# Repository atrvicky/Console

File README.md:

# Console
PCB design of the Hyp Console - an esp8266 powered board, powered by microPython and a ton of embedded functionalities out of the box.

The console has the following features:

* I2C Expander.
* Native LCD support.
* Native support for upto 3 external LEDs (PWM enabled).
* One default LED (PWM enabled).
* Native support for upto 4 DC motors, 2 Steppers, one ultrasound sensor and two infrared sensors.
* Integrated accelerometer with freefall detection, tap detection, doub click detection.
* Dedicated PWM controller and I2C port expander.
* MOSFET controllers for motors for enhanced current delivery to the motors.
* 9 GPIO pins.
* Stabilised 3V3 and 5V outputs.

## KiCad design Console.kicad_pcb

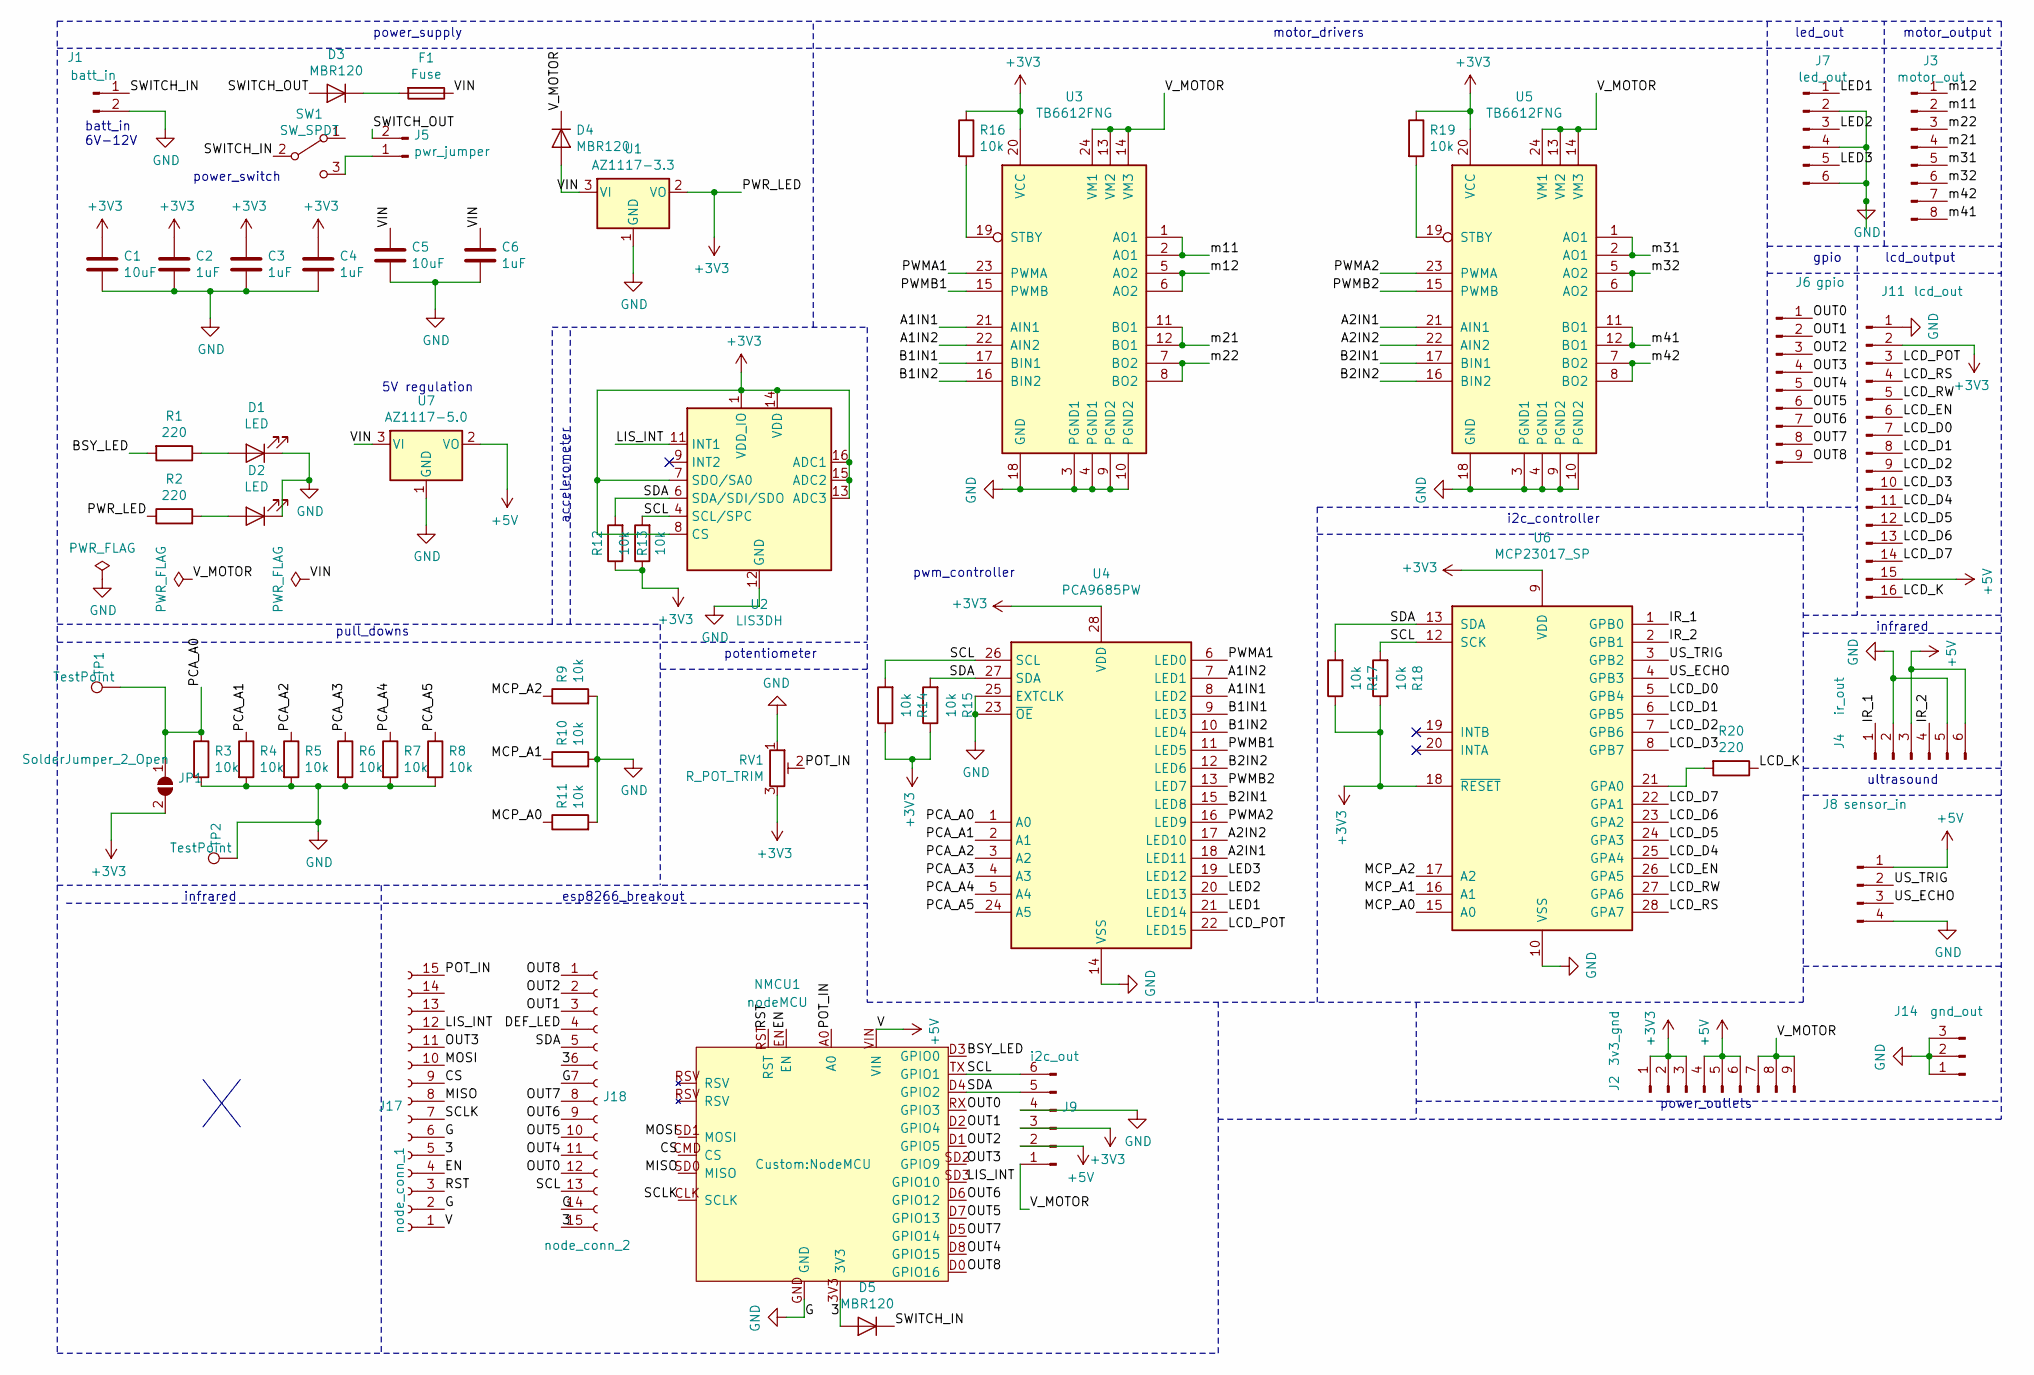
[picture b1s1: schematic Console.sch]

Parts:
C1, C5: 10uF; C_0805_2012Metric
C2, C3, C4, C6: 1uF; C_0805_2012Metric
D1, D2: LED; LED_0805_2012Metric
D3, D4, D5: MBR120; D_0805_2012Metric
F1: Fuse; Fuse_1206_3216Metric
J1: batt_in; PinHeader_1x02_P2.54mm_Vertical
J2: 3v3_gnd; PinHeader_1x09_P2.54mm_Vertical
J3: motor_out; PinHeader_1x08_P2.54mm_Vertical
J4: ir_out; PinHeader_1x06_P2.54mm_Vertical
J5: pwr_jumper; PinHeader_1x02_P2.54mm_Vertical
J6: gpio; PinHeader_1x09_P2.54mm_Vertical
J7: led_out; PinHeader_1x06_P2.54mm_Vertical
J8: sensor_in; PinHeader_1x04_P2.54mm_Vertical
J9: i2c_out; PinHeader_1x06_P2.54mm_Vertical
J11: lcd_out; PinHeader_1x16_P2.54mm_Vertical
J14: gnd_out; PinHeader_1x03_P2.54mm_Vertical
J17: node_conn_1; PinSocket_1x15_P2.54mm_Vertical
J18: node_conn_2; PinSocket_1x15_P2.54mm_Vertical
JP1: SolderJumper_2_Open; SolderJumper-2_P1.3mm_Open_RoundedPad1.0x1.5mm
NMCU1: nodeMCU; NodeMCU
R1, R2, R20: 220; R_0805_2012Metric
R3, R4, R5, R6, R7, R8, R9, R10, R11, R12, R13, R14, R15, R16, R17, R18, R19: 10k; R_0805_2012Metric
RV1: R_POT_TRIM; Potentiometer_Bourns_PTA2043_Single_Slide
SW1: SW_SPDT; SW_CuK_OS102011MA1QN1_SPDT_Angled
TP1, TP2: TestPoint; TestPoint_Pad_1.5x1.5mm
U1: AZ1117-3.3; TO-252-3_TabPin2
U2: LIS3DH; LGA-16_3x3mm_P0.5mm_LayoutBorder3x5y
U3, U5: TB6612FNG; SSOP-24_5.3x8.2mm_P0.65mm
U4: PCA9685PW; TSSOP-28_4.4x9.7mm_P0.65mm
U6: MCP23017_SP; SOIC-28W_7.5x17.9mm_P1.27mm
U7: AZ1117-5.0; TO-252-3_TabPin2

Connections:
+3V3: C1.1, C2.1, C3.1, C4.1, J2.1, J2.2, J2.3, J9.3, J11.2, JP1.2 (B), R2.1, R12.1, R13.1, R14.1, R15.1, R16.1, R17.1, R18.1, R19.1, RV1.3, U1.2 (VO), U2.1 (VDD_IO), U2.7 (SDO/SA0), U2.8 (CS), U2.13 (ADC3), U2.14 (VDD), U2.15 (ADC2), U2.16 (ADC1), U3.20 (VCC), U4.28 (VDD), U5.20 (VCC), U6.9 (VDD), U6.18 (~RESET~); also elsewhere on the board
+5V: J2.4, J2.5, J2.6, J4.3, J4.6, J8.1, J9.2, J11.15, J17.1, NMCU1.VIN, U7.2 (VO)
/3: D5.2 (A), J17.5, J18.6, J18.15, NMCU1.3V3
/A1IN1: U3.21 (AIN1), U4.8 (LED2)
/A1IN2: U3.22 (AIN2), U4.7 (LED1)
/A2IN1: U4.18 (LED11), U5.21 (AIN1)
/A2IN2: U4.17 (LED10), U5.22 (AIN2)
/B1IN1: U3.17 (BIN1), U4.9 (LED3)
/B1IN2: U3.16 (BIN2), U4.10 (LED4)
/B2IN1: U4.15 (LED8), U5.17 (BIN1)
/B2IN2: U4.12 (LED6), U5.16 (BIN2)
/BSY_LED: NMCU1.D3 (GPIO0), R1.2
/CS: J17.9, NMCU1.CMD (CS)
/DEF_LED: J18.4
/EN: J17.4, NMCU1.EN
/IR_1: J4.1, U6.1 (GPB0)
/IR_2: J4.4, U6.2 (GPB1)
/LCD_D0: J11.7, U6.5 (GPB4)
/LCD_D1: J11.8, U6.6 (GPB5)
/LCD_D2: J11.9, U6.7 (GPB6)
/LCD_D3: J11.10, U6.8 (GPB7)
/LCD_D4: J11.11, U6.25 (GPA4)
/LCD_D5: J11.12, U6.24 (GPA3)
/LCD_D6: J11.13, U6.23 (GPA2)
/LCD_D7: J11.14, U6.22 (GPA1)
/LCD_EN: J11.6, U6.26 (GPA5)
/LCD_K: J11.16, R20.1
/LCD_POT: J11.3, U4.22 (LED15)
/LCD_RS: J11.4, U6.28 (GPA7)
/LCD_RW: J11.5, U6.27 (GPA6)
/LED1: J7.1, U4.21 (LED14)
/LED2: J7.3, U4.20 (LED13)
/LED3: J7.5, U4.19 (LED12)
/LIS_INT: J17.12, NMCU1.SD3 (GPIO10), U2.11 (INT1)
/MCP_A0: R11.1, U6.15 (A0)
/MCP_A1: R10.1, U6.16 (A1)
/MCP_A2: R9.1, U6.17 (A2)
/MISO: J17.8, NMCU1.SD0 (MISO)
/MOSI: J17.10, NMCU1.SD1 (MOSI)
/OUT0: J6.1, J18.12, NMCU1.RX (GPIO3)
/OUT1: J6.2, J18.3, NMCU1.D2 (GPIO4)
/OUT2: J6.3, J18.2, NMCU1.D1 (GPIO5)
/OUT3: J6.4, J17.11, NMCU1.SD2 (GPIO9)
/OUT4: J6.5, J18.11, NMCU1.D8 (GPIO15)
/OUT5: J6.6, J18.10, NMCU1.D7 (GPIO13)
/OUT6: J6.7, J18.9, NMCU1.D6 (GPIO12)
/OUT7: J6.8, J18.8, NMCU1.D5 (GPIO14)
/OUT8: J6.9, J18.1, NMCU1.D0 (GPIO16)
/PCA_A0: JP1.1 (A), R3.1, TP1.1, U4.1 (A0)
/PCA_A1: R4.1, U4.2 (A1)
/PCA_A2: R5.1, U4.3 (A2)
/PCA_A3: R6.1, U4.4 (A3)
/PCA_A4: R7.1, U4.5 (A4)
/PCA_A5: R8.1, U4.24 (A5)
/POT_IN: J17.15, NMCU1.A0, RV1.2
/PWMA1: U3.23 (PWMA), U4.6 (LED0)
/PWMA2: U4.16 (LED9), U5.23 (PWMA)
/PWMB1: U3.15 (PWMB), U4.11 (LED5)
/PWMB2: U4.13 (LED7), U5.15 (PWMB)
/RST: J17.3, NMCU1.RST
/SCLK: J17.7, NMCU1.CLK (SCLK)
/SDA: J9.5, J18.5, NMCU1.D4 (GPIO2), R12.2, R15.2, R17.2, U2.6 (SDA/SDI/SDO), U4.27 (SDA), U6.13 (SDA)
/SWITCH_IN: D5.1 (K), J1.1, SW1.2 (B)
/SWITCH_OUT: D3.2 (A), J5.2
/US_ECHO: J8.3, U6.4 (GPB3)
/US_TRIG: J8.2, U6.3 (GPB2)
/VIN: C5.1, C6.1, D4.2 (A), F1.1, U1.3 (VI), U7.3 (VI); also elsewhere on the board
/V_MOTOR: D4.1 (K), J2.7, J2.8, J2.9, J9.1, U3.13 (VM2), U3.14 (VM3), U3.24 (VM1), U5.13 (VM2), U5.14 (VM3), U5.24 (VM1)
/m11: J3.2, U3.1 (AO1), U3.2 (AO1)
/m12: J3.1, U3.5 (AO2), U3.6 (AO2)
/m21: J3.4, U3.11 (BO1), U3.12 (BO1)
/m22: J3.3, U3.7 (BO2), U3.8 (BO2)
/m31: J3.5, U5.1 (AO1), U5.2 (AO1)
/m32: J3.6, U5.5 (AO2), U5.6 (AO2)
/m41: J3.8, U5.11 (BO1), U5.12 (BO1)
/m42: J3.7, U5.7 (BO2), U5.8 (BO2)
GND: C1.2, C2.2, C3.2, C4.2, C5.2, C6.2, D1.1 (K), D2.1 (K), J1.2, J4.2, J4.5, J7.2, J7.4, J7.6, J8.4, J9.4, J11.1, J14.1, J14.2, J14.3, J17.2, J17.6, J18.7, J18.14, NMCU1.GND, R3.2, R4.2, R5.2, R6.2, R7.2, R8.2, R9.2, R10.2, R11.2, RV1.1, TP2.1, U1.1 (GND), U2.5 (GND), U2.10 (GND), U2.12 (GND), U3.3 (PGND1), U3.4 (PGND1), U3.9 (PGND2), U3.10 (PGND2), U3.18 (GND), U4.14 (VSS), U4.23 (~OE), U4.25 (EXTCLK), U5.3 (PGND1), U5.4 (PGND1), U5.9 (PGND2), U5.10 (PGND2), U5.18 (GND), U6.10 (VSS), U7.1 (GND)
unnamed: D1.2 (A), R1.1
unnamed: D2.2 (A), R2.2
unnamed 79: D3.1 (K), F1.2; also elsewhere on the board
unnamed: J5.1, SW1.3 (C)
unnamed: R19.2, U5.19 (STBY)
unnamed: R20.2, U6.21 (GPA0)

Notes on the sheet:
batt_in 6V-12V
power_switch
pull_downs
power_supply
accelerometer
motor_drivers
pwm_controller
potentiometer
i2c_controller
esp8266_breakout
led_out
gpio
ultrasound
lcd_output
infrared
5V regulation
infrared
power_outlets
motor_output

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
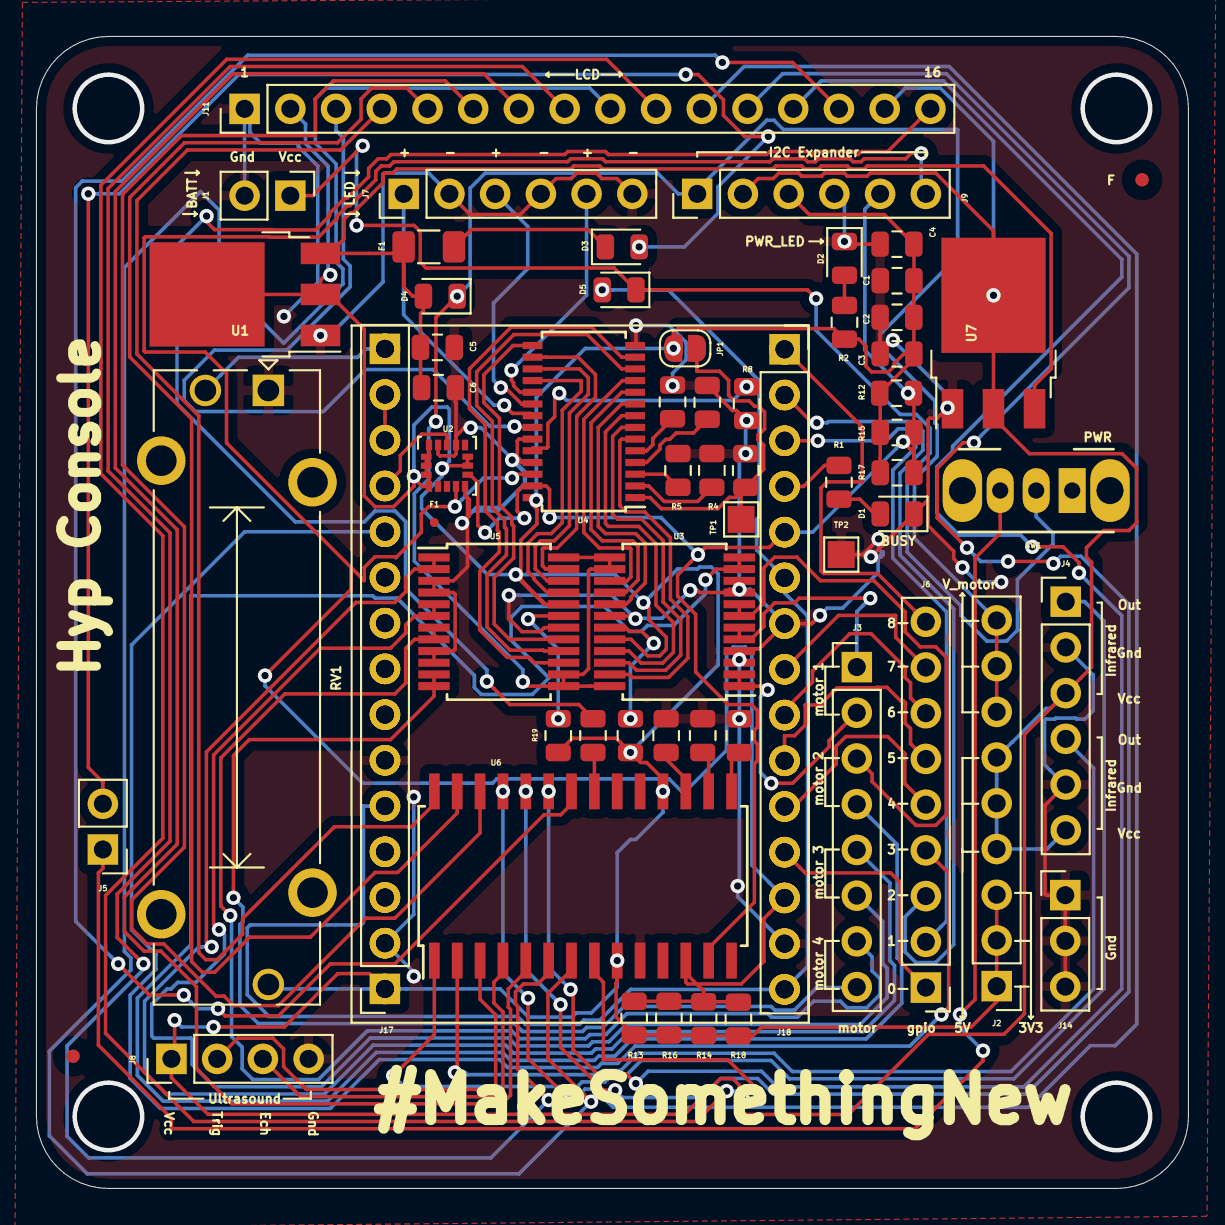
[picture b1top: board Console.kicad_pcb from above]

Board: 2 copper layers, 64.0 x 64.0 mm, 62 parts (0 on the bottom side), 84 nets.

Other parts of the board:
F: Fiducial_0.75mm_Mask2.25mm
F1#2: Fuse; Fuse_1206_3216Metric
F#2: Fiducial_0.75mm_Mask2.25mm
R16#2: 10k; R_0805_2012Metric

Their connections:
+3V3: R16#2.1; also elsewhere on the board
/VIN: F1#2.1; also elsewhere on the board
unnamed 79: F1#2.2; also elsewhere on the board

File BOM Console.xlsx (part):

Source: | G:\Studio\Hardware\kiCad\Console\Console.sch
Date: | 43774.806493055556
Tool: | Eeschema (5.1.0)-1
Generator: | G:\Program Files\KiCad\bin\scripting\plugins/bom_csv_grouped_by_value.py
Component Count: | 56
Individual Components:
Item | Qty | Reference(s) | Value | LibPart | Footprint | Datasheet
 |  | C1 | 10uF | Device:C | Capacitor_SMD:C_0805_2012Metric | ~
 |  | C2 | 1uF | Device:C | Capacitor_SMD:C_0805_2012Metric | ~
 |  | C3 | 1uF | Device:C | Capacitor_SMD:C_0805_2012Metric | ~
 |  | C4 | 1uF | Device:C | Capacitor_SMD:C_0805_2012Metric | ~
 |  | C5 | 10uF | Device:C | Capacitor_SMD:C_0805_2012Metric | ~
 |  | C6 | 1uF | Device:C | Capacitor_SMD:C_0805_2012Metric | ~
 |  | D1 | LED | Device:LED | LED_SMD:LED_0805_2012Metric | ~
 |  | D2 | LED | Device:LED | LED_SMD:LED_0805_2012Metric | ~
 |  | D3 | MBR120 | Device:D | Diode_SMD:D_0805_2012Metric | ~
 |  | D4 | MBR120 | Device:D | Diode_SMD:D_0805_2012Metric | ~
 |  | D5 | MBR120 | Device:D | Diode_SMD:D_0805_2012Metric | ~
 |  | F1 | Fuse | Device:Fuse | Fuse:Fuse_1206_3216Metric | ~
 |  | J1 | batt_in | Connector:Conn_01x02_Male | Connector_PinHeader_2.54mm:PinHeader_1x02_P2.54mm_Vertical | ~
 |  | J2 | 3v3_gnd | Connector:Conn_01x09_Male | Connector_PinHeader_2.54mm:PinHeader_1x09_P2.54mm_Vertical | ~
 |  | J3 | motor_out | Connector:Conn_01x08_Male | Connector_PinHeader_2.54mm:PinHeader_1x08_P2.54mm_Vertical | ~
 |  | J4 | ir_out | Connector:Conn_01x06_Male | Connector_PinHeader_2.54mm:PinHeader_1x06_P2.54mm_Vertical | ~
 |  | J5 | pwr_jumper | Connector:Conn_01x02_Male | Connector_PinHeader_2.54mm:PinHeader_1x02_P2.54mm_Vertical | ~
 |  | J6 | gpio | Connector:Conn_01x09_Male | Connector_PinHeader_2.54mm:PinHeader_1x09_P2.54mm_Vertical | ~
 |  | J7 | led_out | Connector:Conn_01x06_Male | Connector_PinHeader_2.54mm:PinHeader_1x06_P2.54mm_Vertical | ~
 |  | J8 | sensor_in | Connector:Conn_01x04_Male | Connector_PinHeader_2.54mm:PinHeader_1x04_P2.54mm_Vertical | ~
 |  | J9 | i2c_out | Connector:Conn_01x06_Male | Connector_PinHeader_2.54mm:PinHeader_1x06_P2.54mm_Vertical | ~
 |  | J11 | lcd_out | Connector:Conn_01x16_Male | Connector_PinHeader_2.54mm:PinHeader_1x16_P2.54mm_Vertical | ~
 |  | J14 | gnd_out | Connector:Conn_01x03_Male | Connector_PinHeader_2.54mm:PinHeader_1x03_P2.54mm_Vertical | ~
 |  | J17 | node_conn_1 | Connector:Conn_01x15_Female | Connector_PinSocket_2.54mm:PinSocket_1x15_P2.54mm_Vertical | ~
 |  | J18 | node_conn_2 | Connector:Conn_01x15_Female | Connector_PinSocket_2.54mm:PinSocket_1x15_P2.54mm_Vertical | ~
 |  | JP1 | SolderJumper_2_Open | Jumper:SolderJumper_2_Open | Jumper:SolderJumper-2_P1.3mm_Open_RoundedPad1.0x1.5mm | ~
 |  | NMCU1 | nodeMCU | MCU_Espressif:nodeMCU | Custom:NodeMCU
 |  | R1 | 220 | Device:R | Resistor_SMD:R_0805_2012Metric | ~
 |  | R2 | 220 | Device:R | Resistor_SMD:R_0805_2012Metric | ~
 |  | R3 | 10k | Device:R | Resistor_SMD:R_0805_2012Metric | ~
 |  | R4 | 10k | Device:R | Resistor_SMD:R_0805_2012Metric | ~
 |  | R5 | 10k | Device:R | Resistor_SMD:R_0805_2012Metric | ~
 |  | R6 | 10k | Device:R | Resistor_SMD:R_0805_2012Metric | ~
 |  | R7 | 10k | Device:R | Resistor_SMD:R_0805_2012Metric | ~
 |  | R8 | 10k | Device:R | Resistor_SMD:R_0805_2012Metric | ~
 |  | R9 | 10k | Device:R | Resistor_SMD:R_0805_2012Metric | ~
 |  | R10 | 10k | Device:R | Resistor_SMD:R_0805_2012Metric | ~
 |  | R11 | 10k | Device:R | Resistor_SMD:R_0805_2012Metric | ~
 |  | R12 | 10k | Device:R | Resistor_SMD:R_0805_2012Metric | ~
 |  | R13 | 10k | Device:R | Resistor_SMD:R_0805_2012Metric | ~
 |  | R14 | 10k | Device:R | Resistor_SMD:R_0805_2012Metric | ~
 |  | R15 | 10k | Device:R | Resistor_SMD:R_0805_2012Metric | ~
 |  | R16 | 10k | Device:R | Resistor_SMD:R_0805_2012Metric | ~
 |  | R17 | 10k | Device:R | Resistor_SMD:R_0805_2012Metric | ~
 |  | R18 | 10k | Device:R | Resistor_SMD:R_0805_2012Metric | ~
 |  | R19 | 10k | Device:R | Resistor_SMD:R_0805_2012Metric | ~
 |  | R20 | 220 | Device:R | Resistor_SMD:R_0805_2012Metric | ~
 |  | RV1 | R_POT_TRIM | Device:R_POT_TRIM | Potentiometer_THT:Potentiometer_Bourns_PTA2043_Single_Slide | ~
 |  | SW1 | SW_SPST | Switch:SW_SPST | Button_Switch_SMD:SW_DIP_SPSTx01_Slide_9.78x4.72mm_W8.61mm_P2.54mm | ~
 |  | U1 | AZ1117-3.3 | Regulator_Linear:AZ1117-3.3 | Package_TO_SOT_SMD:TO-252-3_TabPin2 | https://www.diodes.com/assets/Datasheets/AZ1117.pdf
 |  | U2 | LIS3DH | Sensor_Motion:LIS3DH | Package_LGA:LGA-16_3x3mm_P0.5mm_LayoutBorder3x5y | https://www.st.com/resource/en/datasheet/cd00274221.pdf
 |  | U3 | TB6612FNG | Driver_Motor:TB6612FNG | Package_SO:SSOP-24_5.3x8.2mm_P0.65mm | https://toshiba.semicon-storage.com/us/product/linear/motord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
 |  | U4 | PCA9685PW | Driver_LED:PCA9685PW | Package_SO:TSSOP-28_4.4x9.7mm_P0.65mm | http://www.nxp.com/documents/data_sheet/PCA9685.pdf
 |  | U5 | TB6612FNG | Driver_Motor:TB6612FNG | Package_SO:SSOP-24_5.3x8.2mm_P0.65mm | https://toshiba.semicon-storage.com/us/product/linear/motord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
 |  | U6 | MCP23017_SP | Interface_Expansion:MCP23017_SP | Package_SO:SOIC-28W_7.5x17.9mm_P1.27mm | http://ww1.microchip.com/downloads/en/DeviceDoc/20001952C.pdf
 |  | U7 | AZ1117-5.0 | Regulator_Linear:AZ1117-5.0 | Package_TO_SOT_SMD:TO-252-3_TabPin2 | https://www.diodes.com/assets/Datasheets/AZ1117.pdf
Collated Components:
Item | Qty | Reference(s) | Value | LibPart | Footprint | Datasheet
1 | 2 | C1, C5 | 10uF | Device:C | Capacitor_SMD:C_0805_2012Metric | ~
2 | 4 | C2, C3, C4, C6 | 1uF | Device:C | Capacitor_SMD:C_0805_2012Metric | ~
3 | 2 | D1, D2 | LED | Device:LED | LED_SMD:LED_0805_2012Metric | ~
4 | 3 | D3, D4, D5 | MBR120 | Device:D | Diode_SMD:D_0805_2012Metric | ~
5 | 1 | F1 | Fuse | Device:Fuse | Fuse:Fuse_1206_3216Metric | ~
6 | 1 | J1 | batt_in | Connector:Conn_01x02_Male | Connector_PinHeader_2.54mm:PinHeader_1x02_P2.54mm_Vertical | ~
7 | 1 | J2 | 3v3_gnd | Connector:Conn_01x09_Male | Connector_PinHeader_2.54mm:PinHeader_1x09_P2.54mm_Vertical | ~
8 | 1 | J3 | motor_out | Connector:Conn_01x08_Male | Connector_PinHeader_2.54mm:PinHeader_1x08_P2.54mm_Vertical | ~
9 | 1 | J4 | ir_out | Connector:Conn_01x06_Male | Connector_PinHeader_2.54mm:PinHeader_1x06_P2.54mm_Vertical | ~
10 | 1 | J5 | pwr_jumper | Connector:Conn_01x02_Male | Connector_PinHeader_2.54mm:PinHeader_1x02_P2.54mm_Vertical | ~
11 | 1 | J6 | gpio | Connector:Conn_01x09_Male | Connector_PinHeader_2.54mm:PinHeader_1x09_P2.54mm_Vertical | ~
12 | 1 | J7 | led_out | Connector:Conn_01x06_Male | Connector_PinHeader_2.54mm:PinHeader_1x06_P2.54mm_Vertical | ~
13 | 1 | J8 | sensor_in | Connector:Conn_01x04_Male | Connector_PinHeader_2.54mm:PinHeader_1x04_P2.54mm_Vertical | ~
14 | 1 | J9 | i2c_out | Connector:Conn_01x06_Male | Connector_PinHeader_2.54mm:PinHeader_1x06_P2.54mm_Vertical | ~
15 | 1 | J11 | lcd_out | Connector:Conn_01x16_Male | Connector_PinHeader_2.54mm:PinHeader_1x16_P2.54mm_Vertical | ~
16 | 1 | J14 | gnd_out | Connector:Conn_01x03_Male | Connector_PinHeader_2.54mm:PinHeader_1x03_P2.54mm_Vertical | ~
17 | 1 | J17 | node_conn_1 | Connector:Conn_01x15_Female | Connector_PinSocket_2.54mm:PinSocket_1x15_P2.54mm_Vertical | ~
18 | 1 | J18 | node_conn_2 | Connector:Conn_01x15_Female | Connector_PinSocket_2.54mm:PinSocket_1x15_P2.54mm_Vertical | ~
19 | 1 | JP1 | SolderJumper_2_Open | Jumper:SolderJumper_2_Open | Jumper:SolderJumper-2_P1.3mm_Open_RoundedPad1.0x1.5mm | ~
20 | 1 | NMCU1 | nodeMCU | MCU_Espressif:nodeMCU | Custom:NodeMCU
21 | 3 | R1, R2, R20 | 220 | Device:R | Resistor_SMD:R_0805_2012Metric | ~
22 | 17 | R3, R4, R5, R6, R7, R8, R9, R10, R11, R12, R13, R14, R15, R16, R17, R18, R19 | 10k | Device:R | Resistor_SMD:R_0805_2012Metric | ~
23 | 1 | RV1 | R_POT_TRIM | Device:R_POT_TRIM | Potentiometer_THT:Potentiometer_Bourns_PTA2043_Single_Slide | ~
24 | 1 | SW1 | SW_SPST | Switch:SW_SPST | Button_Switch_SMD:SW_DIP_SPSTx01_Slide_9.78x4.72mm_W8.61mm_P2.54mm | ~
25 | 1 | U1 | AZ1117-3.3 | Regulator_Linear:AZ1117-3.3 | Package_TO_SOT_SMD:TO-252-3_TabPin2 | https://www.diodes.com/assets/Datasheets/AZ1117.pdf
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
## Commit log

2019-04-22 Add basic description
2019-04-22 Design 2.0.1 finalised
    Added the following functionalities
    * I2C Expander.
    * Native LCD support.
    * Native support for upto 3 external LEDs (PWM enabled).
    * One default LED (PWM enabled).
    * Native support for upto 4 DC motors, 2 Steppers, one ultrasound sensor and two infrared sensors.
2019-04-27 Add Busy LED
    Changed the DEF_LED to BSY_LED to indicate network business. The default led in the breakout board remains the same.
2019-04-28 Generated gerbers
2019-05-16 Updated for production
    Changed the pad and silkScreen overlap in some places
2019-05-20 Changed Switch footprint
    Changed the switch to SPDT and its footprint to a mouser available switch and made all the legends visible. Added a testpoint for gnd. Final Check yet to be done
2019-05-20 Design approved for production
2019-05-21 removed residue after modifying the switch
2019-05-22 Updated the board size
    Using a pitch of 8mm,the drills were adjusted and the board size was standardized to 64x64
2019-07-30 About production
2019-08-11 Change NodeMCU Vin
    Update the nodeMcu supply voltage to 5v from 3v3
